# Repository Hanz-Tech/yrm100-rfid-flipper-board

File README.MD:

# YRM100 UHF RFID Flipper Zero Hat

A hat-style adapter PCB that plugs directly into the **Flipper Zero** and connects to the **YRM100/1/2/3 UHF RFID module**, enabling long-range RFID reading/writing out of the box.
Works with YRM1001/YRM1002/YRM1003 boards.

Available for purchase from [Tindie](https://www.tindie.com/products/hanztech/flipper-zero-uhf-rfid-yrm100x-adapter/) or [Etsy](https://www.etsy.com/ca/listing/4545558711/flipper-zero-uhf-rfid-yrm100x-adapter)

## Overview

This adapter board bridges the Flipper Zero's GPIO headers to the YRM100 UHF RFID module via a plug-and-play form factor. It provides:

- **5V power** and **3.3V logic** from the Flipper Zero
- **Crossed UART** (TX ↔ RX) for serial communication with the YRM100

- **Power switch** 

## Images

## Connectors

### Flipper Zero (2× 1×8 headers, 2.54 mm pitch)

| Pin | Signal | Pin | Signal |
|-----|--------|-----|--------|
| 1 | **5V** | 9 | **3.3V** |
| 2 | PC0 (GPIO) | 10 | SWC |
| 3 | PC1 (GPIO) | 11 | GND |
| 4 | PC2 (GPIO) | 12 | SIO |
| 5 | PC3 (GPIO) | 13 | **TX** → YRM100 RX |
| 6 | PB3 (GPIO) | 14 | **RX** ← YRM100 TX |
| 7 | PB2 (GPIO) | 15 | C1 |
| 8 | **GND** | 16 | C0 |

> **Note:** UART is crossed — Flipper TX (Pin 13) connects to YRM100 RX, and Flipper RX (Pin 14) connects to YRM100 TX.

### YRM100 Module (5-pin JST 1.25 mm pitch)

| Pin | Signal |
|-----|--------|
| 1 | 5V |
| 2 | GND |
| 3 | TX |
| 4 | RX |
| 5 | EN (pulled up to 3.3V via 10 kΩ) |

## Files

| File | Description |
|------|-------------|
| `yrm100_adapter.kicad_sch` | Schematic (KiCad 9.0) |
| `yrm100_adapter.kicad_pcb` | PCB layout (KiCad 9.0) |
| `yrm100_adapter.kicad_pro` | Project settings and design rules |

## Building / Ordering

1. Open `yrm100_adapter.kicad_pcb` in KiCad 9.0+
2. Run **Design Rules Check** (DRC) — should report zero violations
3. Run **Electrical Rules Check** (ERC) on the schematic — should report zero errors
4. Export **Gerber files** and **drill files** for PCB fabrication
5. Generate **BOM** and **position file** for component assembly

> **Note:** Verify exact footprints and component values against the schematic before ordering. Use the KiCad BOM generator for a complete parts list.

## License

MIT License

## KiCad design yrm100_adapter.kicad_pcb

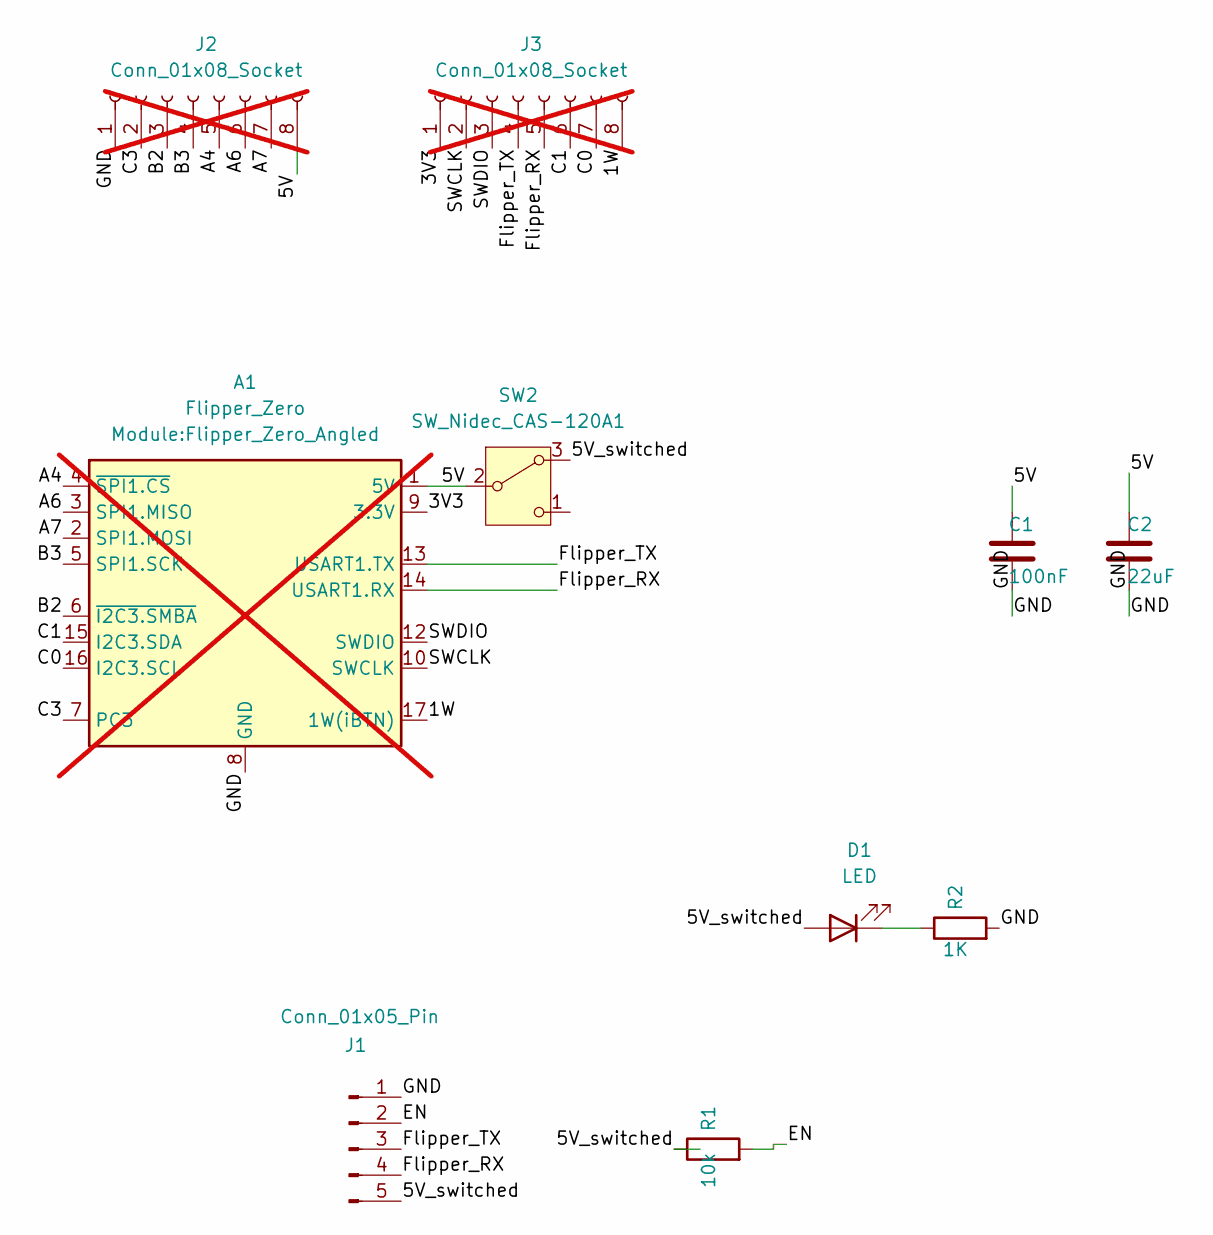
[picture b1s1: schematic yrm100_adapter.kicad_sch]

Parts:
A1: Flipper_Zero; Flipper_Zero_Angled; not fitted
C1: 100nF; C_0603_1608Metric; MPN CC0603KRX7R9BB104; LCSC C14663
C2: 22uF; C_1206_3216Metric; MPN CL31A226KAHNNNE; LCSC C12891
D1: LED; LED_0805_2012Metric; MPN KT-0805G; LCSC C2297
J1: Conn_01x05_Pin; CONN-SMD_5P-P1.25_1.25T-5PWT; MPN 1.25T-5P; LCSC C22076
J2, J3: Conn_01x08_Socket; PinHeader_1x08_P2.54mm_Vertical; not fitted
R1: 10k; R_0603_1608Metric; MPN 0805W8F1002T5E; LCSC C17414
R2: 1K; R_0603_1608Metric; MPN 0603WAF1001T5E; LCSC C21190
SW2: SW_Nidec_CAS-120A1; SW-SMD_K3-1235S-K1; LCSC C92660

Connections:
/1W: A1.17 (1W(iBTN)), J3.8
/3V3: A1.9 (3.3V), J3.1
/5V: A1.1 (5V), C1.1, C2.1, J2.8, SW2.2 (B)
/5V_switched: D1.2 (A), J1.5, R1.1, SW2.3 (A)
/A4: A1.4 (~SPI1.CS), J2.5
/A6: A1.3 (SPI1.MISO), J2.6
/A7: A1.2 (SPI1.MOSI), J2.7
/B2: A1.6 (~I2C3.SMBA), J2.3
/B3: A1.5 (SPI1.SCK), J2.4
/C0: A1.16 (I2C3.SCL), J3.7
/C1: A1.15 (I2C3.SDA), J3.6
/C3: A1.7 (PC3), J2.2
/EN: J1.2, R1.2
/Flipper_RX: A1.14 (USART1.RX), J1.4, J3.5
/Flipper_TX: A1.13 (USART1.TX), J1.3, J3.4
/GND: A1.8 (GND), A1.11 (GND), A1.18 (GND), C1.2, C2.2, J1.1, J2.1, R2.2
/SWCLK: A1.10 (SWCLK), J3.2
/SWDIO: A1.12 (SWDIO), J3.3
unnamed: D1.1 (K), R2.1

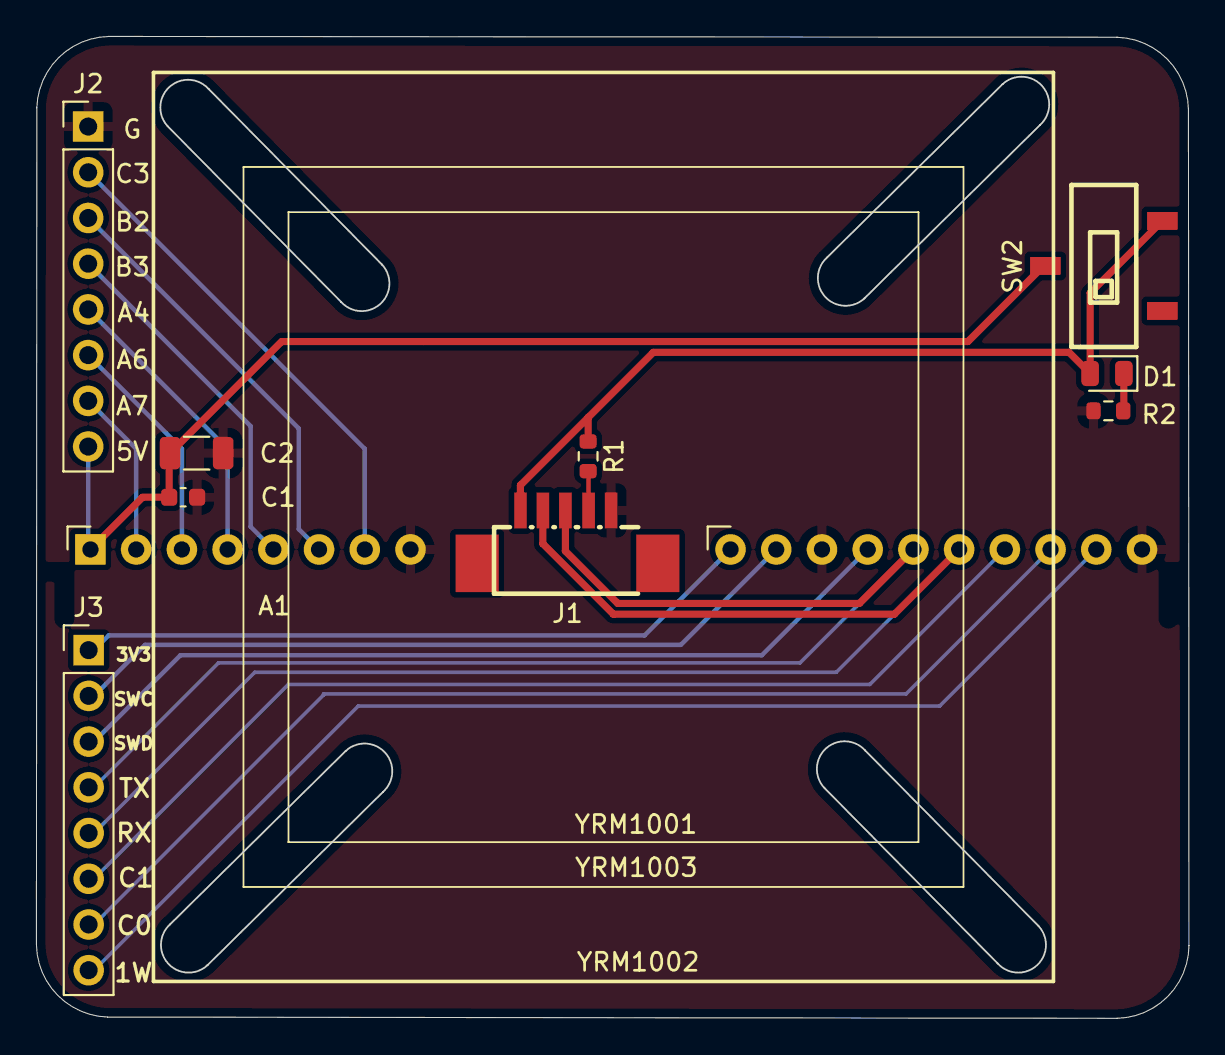
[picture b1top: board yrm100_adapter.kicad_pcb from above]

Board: 2 copper layers, 64.0 x 54.5 mm, 10 parts (0 on the bottom side), 19 nets.

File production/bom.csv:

Designator,Footprint,Quantity,Value,LCSC Part #
C1,0603,1,100nF,C14663
C2,1206,1,22uF,C12891
D1,0805,1,LED,C2297
J1,CONN-SMD_5P-P1.25_1.25T-5PWT,1,Conn_01x05_Pin,C22076
R1,0603,1,10k,C17414
R2,0603,1,1K,C21190
SW2,SW-SMD_K3-1235S-K1,1,SW_Nidec_CAS-120A1,C92660

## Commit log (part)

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2026-06-12 add 3d cad model
2026-06-13 move position of headers
2026-06-27 Update with images
